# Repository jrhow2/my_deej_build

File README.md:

# jrhow2's Deej Build
## Description

This is a repository to document and share my work on my first Deej build, which includes 1 rotary potentiometer for master volume, 5 slide potentiometers, 6 latching mute 
buttons with LED indicators (one for each slider), and a 12-key macropad. This is primarily based on [miodec's fork](https://github.com/Miodec/deej), which 
adds support for programmable buttons to the original deej project from [omiharel](https://github.com/omriharel/deej).

The main additions I have made to these projects are the use of the [keypad.h](https://github.com/Chris--A/Keypad) library to increase the number of
programmable buttons past what would be achievable using the arduino nano's pins for individual buttons, and the use of latching led as mute buttons/LED indicators. An autohotkey script was used to expand the functionality of the programmable buttons, and a custom PCB was created to more easily add the macropad keyswitches.

In this repository, I've included that CAD files for the enclosure produced in Fusion360, the PCB schematics and gerber files, the customized arduino sketch, and the autohotkey script.

## Wokwi Cicuit design/code simulation
[Wokwi.com](https://wokwi.com) was used for circuit design and siumlation of the Arduino Nano and code. The Wokwi simulation can be found [here](https://wokwi.com/projects/416743878244643841), and the .zip files exported from Wokwi can be found at [deej_jrhow2_wokwi.zip](deej_jrhow2_wokwi.zip).

Note that since wokwi does not include latching buttons and because there was some difficulty with how I soldered my sliders in the final configuration, the code in wokwi does not exactly match the final code in the [provided .ino file](jrhow2s_deej.ino).

## [Mechancal Design](mechanical_design)
### Fusion 360 design files
The enclosure was designed in Fusion 360, and I've provided the [.f3d file](mechanical_design/f360_jrhow2's_deej.f3d).
### 3D printing
Slicing was performed in [Orca Slicer](https://github.com/SoftFever/OrcaSlicer) and the models were printed on a BambuLab P1S with an AMS unit for multi-color printing. I have provided the [Orca Slicer project file](mechanical_design/orca-slicer_jrhow2's_deej.3mf) as well as the [.stls](mechanical_design/STLs) of all of the parts.

To get the faux carbon fiber look on the top surface, I used [this textured plate](https://www.amazon.com/gp/product/B0CP5X3H2Z/ref=ppx_yo_dt_b_search_asin_title?ie=UTF8&psc=1) purchased from Amazon. These kinds of plates work best with slightly increased bed temperature and decreased speed for the first layer or two.

### Part's list
- [5x 60 mm Slide Potentiometers](https://www.amazon.com/dp/B07PNDLKQQ?ref_=ppx_hzsearch_conn_dt_b_fed_asin_title_1)
- [1x Rotary Potentiometer](https://www.amazon.com/dp/B07B64MWRF?ref_=ppx_hzsearch_conn_dt_b_fed_asin_title_2)
- [12x Cherry MX brown keyswitches](https://www.amazon.com/Cherry-MX-RGB-Mechanical-Keyboard/dp/B0CBS5M29R/ref=sr_1_2_sspa?crid=1GYDEP9RCY5T0&dib=eyJ2IjoiMSJ9.CN8d0MrS5DmQJVn-3xpAB0mhQuQKi8KCveO0JcbJzXpjdPU5HlAwrbz5tbdCWk3kthYGaP7PowyWtKo4o5DwA8xeNte1qEcJPl-tHwgDbC15iH93cMmkFZe0xWSh1AFUqjXYJmBKIA4P6uL1rWdwi3rx7YHnh_XPOvBDt01OFRK_tM1kTGipKEFM-LWU1gadXluddE0z2FO6sqxmrbP47VR9et4cIyCPHad9PMV20qwvgUSGjHwJ7VQUZ6RM5yiMxK3H-e-PVNU_TkNI8w8Ro4aga5POcPGEx3rvmk47ERo.JgLyCq7_-X_gLAnXje8SgQaPr5BdVQ0jFXflrShL0JE&dib_tag=se&keywords=cherry%2Bmx%2Bbrown%2Bkeyswitch&qid=1738734329&s=industrial&sprefix=cherry%2Bmx%2Bbrown%2Bkeyswitc%2Cindustrial%2C157&sr=1-2-spons&sp_csd=d2lkZ2V0TmFtZT1zcF9hdGY&smid=AK7PAPV76H5NA&th=1) (or similar)
- [6x Latching 12mm latching button with LED](https://www.amazon.com/dp/B09YLXBHF6?ref_=ppx_hzsearch_conn_dt_b_fed_asin_title_3&th=1) (2 per order)
- [Assort M2 screws](https://www.amazon.com/dp/B0BXS4SXYC?ref_=ppx_hzsearch_conn_dt_b_fed_asin_title_2) (a few of the holes are a bit shallower than others)
- [Elegoo Arduino Nano](https://www.amazon.com/ELEGOO-Arduino-ATmega328P-Without-Compatible/dp/B0713XK923/ref=sr_1_1_sspa?crid=2MQMFAE0FY1Z8&dib=eyJ2IjoiMSJ9.2thvq2A9ZsB75nwbFEpKLNare4EarLgE4_F7j-Bub2L3Dptzgt_789kuIaDLa3JEZPx4hOx-0XsgtrCr5ODgtectiKpfiS-EwMLYMbTm3-1Y0Ps6ziLABlBeyZnuvERKeSZlDR1-K9arOfYLnbvjHKibeIq8u-NfcilkmMGuvIkGhDF-UnZcuOMcGDx1Z1ZpTYCzasz53JTGUo3VJkckAOlmqv41opV5_m7QzFCSfjfq8PhjfRpXVy0oFbJLJ7DgswiqRYJJaj3ZVvBrdKsxvUVHj_74kFZ13D37oFWgwb4.3IOTlCk3ZtmxhoVleWZvcktHRexhEUHSoUZvN_WBMHw&dib_tag=se&keywords=elegoo+nano&qid=1738734462&s=industrial&sprefix=elegoo+nano%2Cindustrial%2C186&sr=1-1-spons&sp_csd=d2lkZ2V0TmFtZT1zcF9hdGY&psc=1)
- Wires, Solder, soldering iron, etc.

### 3D-printed Keycaps
I used [this parametric keycap generator](https://github.com/rsheldiii/KeyV2) with OpenSCAD to make flat keycaps for AMS printing with logos.

## PCB Design
I designed a keypad in KiCad. The PCB is very simple, just connecting the keyswitches together and including some contacts to solder on wires. The pcb files can be found [here](PCB/).

## Arduino Sketch
As mentioned above, my sketch is modified from [miodec's fork](https://github.com/Miodec/deej) by adding support for mute buttons and a keypad. The sketch can be found [here](arduino/jrhow2_deej/).

## Autohotkey script
I used Autohotkey to take the simple keyboard events sent by the arduino sketch and use them to support slightly more complex actions, such as launching apps and a "rage quit" button (just presses alt+f4). In [my config file](config.yaml), I tell Deej to send values for keys that are not commonly used by windows (e.g. "browser home"). Autohotkey then reads these and performs the desired actions. The autohotkey script can be found [here](autohotkey/deej_keys.ahk).

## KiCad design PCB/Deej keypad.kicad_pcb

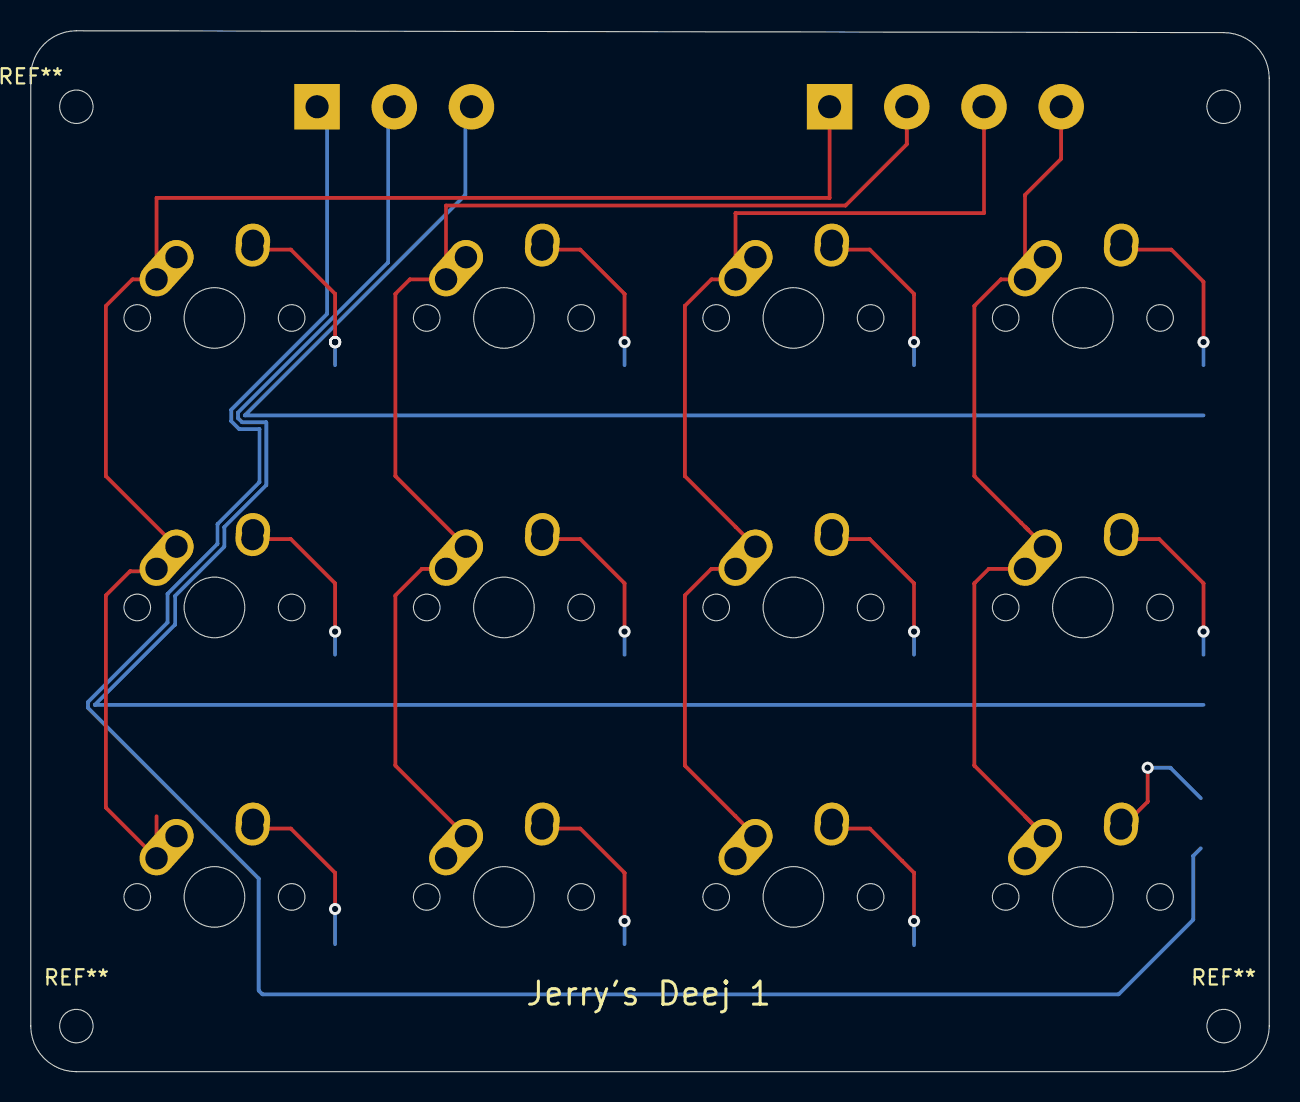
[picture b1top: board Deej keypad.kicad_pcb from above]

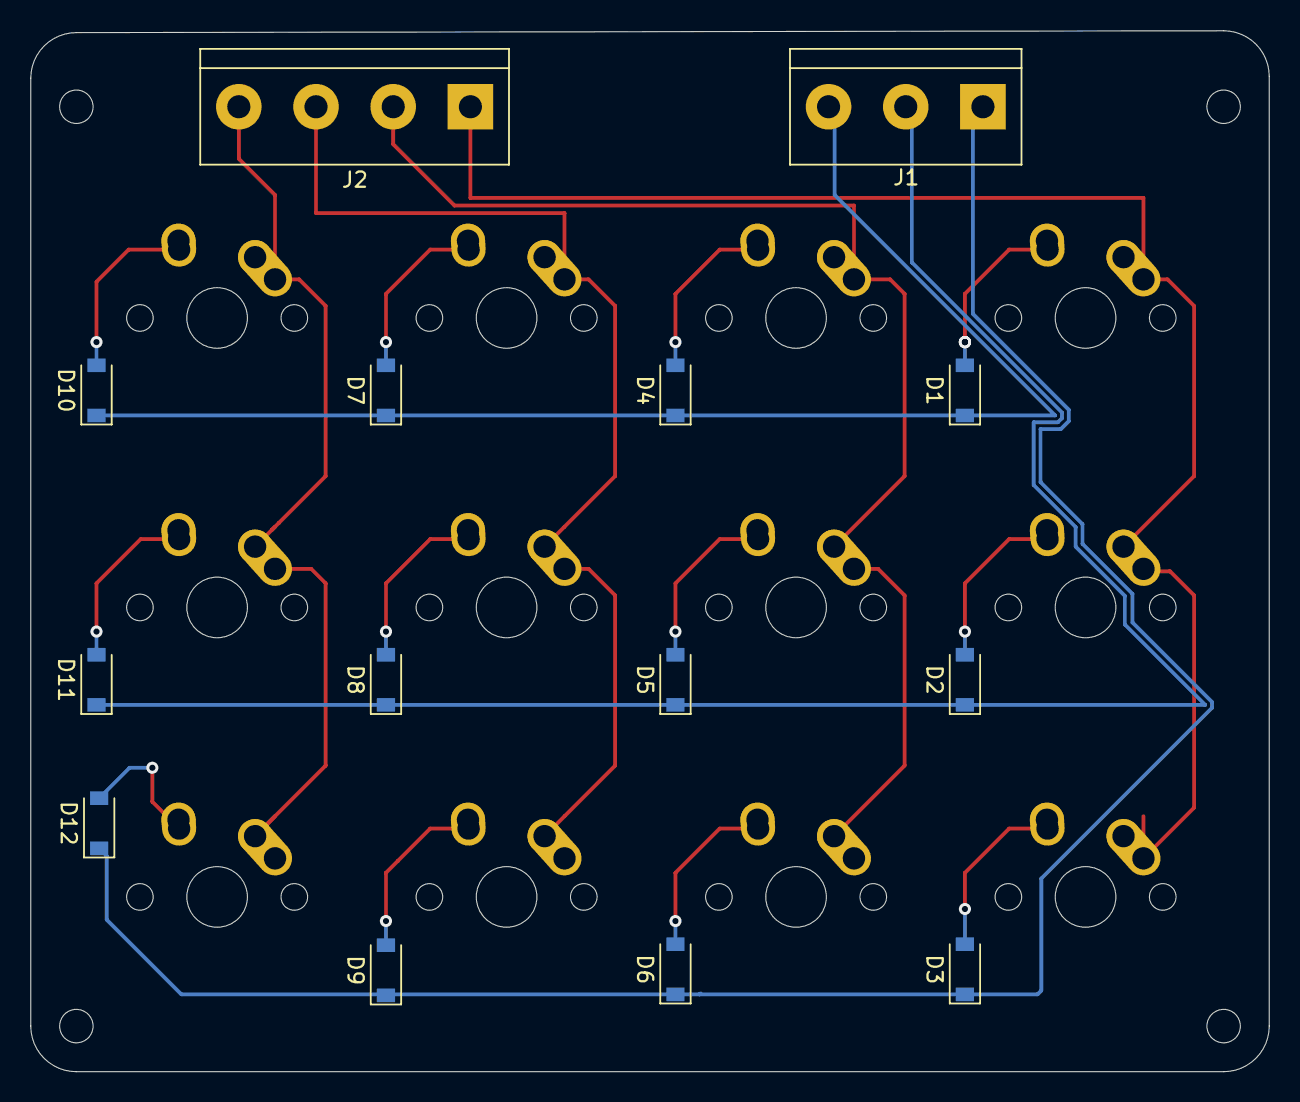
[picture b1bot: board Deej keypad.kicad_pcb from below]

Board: 2 copper layers, 81.5 x 68.5 mm, 26 parts (14 on the bottom side), 19 nets.

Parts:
D1, D2, D3, D4, D5, D6, D7, D8, D9, D10, D11, D12: D_Small; D_SOD-123
J1: Screw_Terminal_01x03; TerminalBlock_bornier-3_P5.08mm
J2: Screw_Terminal_01x04; TerminalBlock_bornier-4_P5.08mm
MX1, MX2, MX3, MX4, MX5, MX6, MX7, MX8, MX9, MX10, MX11, MX12: MX-NoLED; MX-1U-NoLED

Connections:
COL0: J2.1, MX1.1, MX2.1, MX3.1
COL1: J2.2, MX4.1, MX5.1, MX6.1
COL2: J2.3, MX7.1, MX8.1, MX9.1
COL3: J2.4, MX10.1, MX11.1, MX12.1
unnamed: D1.2, MX1.2
unnamed: D2.2, MX2.2
unnamed: D3.2, MX3.2
unnamed: D4.2, MX4.2
unnamed: D5.2, MX5.2
unnamed: D6.2, MX6.2
unnamed: D7.2, MX7.2
unnamed: D8.2, MX8.2
unnamed: D9.2, MX9.2
unnamed: D10.2, MX10.2
unnamed: D11.2, MX11.2
unnamed: D12.2, MX12.2
ROW0: D3.1, D6.1, D9.1, D12.1, J1.1
ROW1: D2.1, D5.1, D8.1, D11.1, J1.2
ROW2: D1.1, D4.1, D7.1, D10.1, J1.3

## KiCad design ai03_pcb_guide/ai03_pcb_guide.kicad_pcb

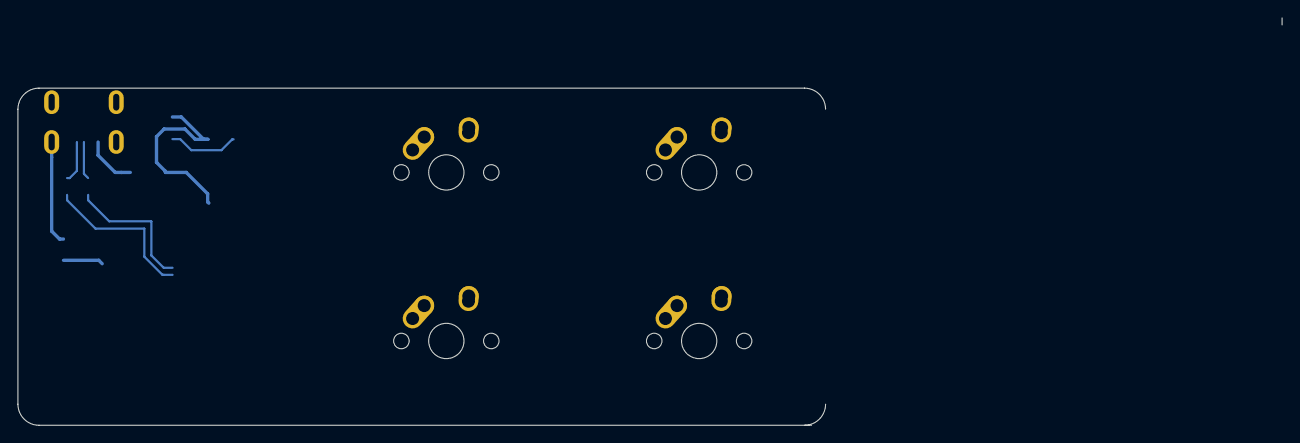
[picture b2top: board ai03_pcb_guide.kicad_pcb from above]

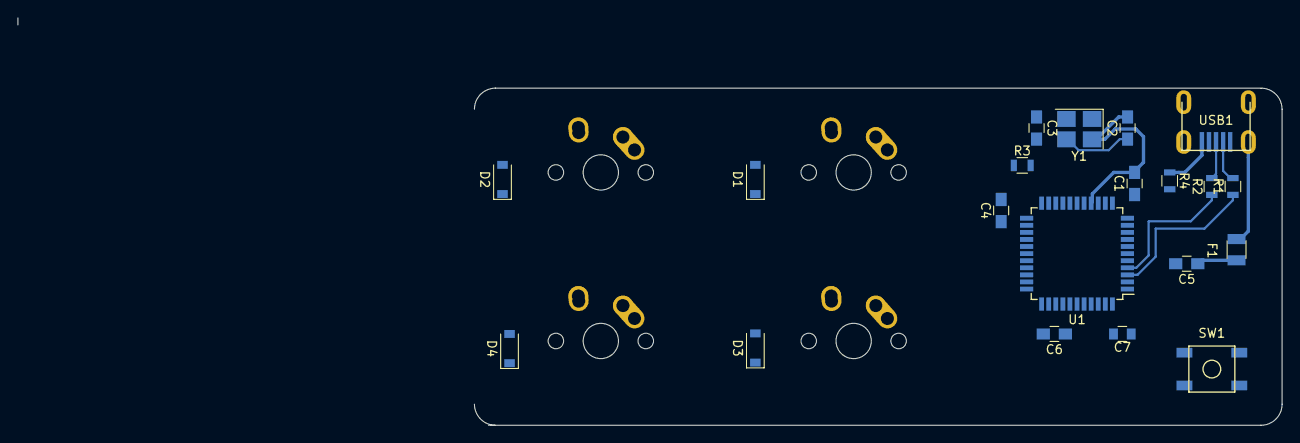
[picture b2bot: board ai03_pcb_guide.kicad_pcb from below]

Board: 2 copper layers, 142.9 x 46.0 mm, 24 parts (20 on the bottom side), 20 nets.

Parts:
C1, C4, C5: 0.1 uF; C_0805_HandSoldering
C2, C3: 22pF; C_0805_HandSoldering
C6: 1 uF; C_0805_HandSoldering
C7: 10 uF; C_0805
D1, D2, D3, D4: D_Small; D_SOD-123
F1: 500 mA; Fuse_SMD1206_Reflow
MX1, MX2, MX3, MX4: MX-NoLED; MX-1.5U-NoLED
R1, R2: 22; R_0805
R3, R4: 10k; R_0805
SW1: SW_Push; SKQG-1155865
U1: ATmega32U4-AU; TQFP-44_10x10mm_Pitch0.8mm
USB1: Molex-0548190589
Y1: 16 MHz; Crystal_SMD_3225-4pin_3.2x2.5mm_HandSoldering

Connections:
+5V: C1.1, C4.1, C5.1, C7.1, F1.1, R3.1, U1.2, U1.7, U1.14, U1.24, U1.34, U1.44
COL0: MX1.1, MX2.1
COL1: MX3.1, MX4.1
D+: R2.2, USB1.3
D-: R1.2, USB1.4
GND: C1.2, C2.2, C3.2, C4.2, C5.2, C6.2, C7.2, R4.1, SW1.1, U1.5, U1.15, U1.23, U1.35, U1.43, USB1.1, Y1.2, Y1.4
unnamed: C2.1, U1.16, Y1.3
unnamed: C3.1, U1.17, Y1.1
unnamed: C6.1, U1.6
unnamed: D1.2, MX1.2
unnamed: D2.2, MX2.2
unnamed: D3.2, MX3.2
unnamed: D4.2, MX4.2
unnamed: R1.1, U1.3
unnamed: R2.1, U1.4
unnamed: R3.2, SW1.2, U1.13
unnamed: R4.2, U1.33
ROW0: D1.1, D3.1
ROW1: D2.1, D4.1
VCC: F1.2, USB1.6

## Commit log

2024-12-09 Initializing with KiCad files
2024-12-09 Add submodules
2024-12-09 Switched to older version for compatibility with guide
2024-12-09 Added libraries to pcb editor
2024-12-09 Started designing PCB for deej keypad
2024-12-09 saving changes
2025-01-01 Uploaded main files for running deej
    Uploaded config.yaml, autohotkey script, and arduino sketch.
2025-01-02 Added wokwi zip archive
2025-01-02 Rename Deej_Soldered.ino to jrhow2s_deej.ino
2025-01-02 Rename Jrhow2's Deej.f3d to Mechanical Design/Jrhow2's Deej.f3d
2025-01-02 Rename Deej top face 20241220.3mf to jrhow2's deej.3mf
2025-01-02 Rename mechanical_design/Badge_support.stl to mechanical_design/STLs/badge_support.stl
2025-01-02 Rename mechanical_design/Key Frame.step.stl to mechanical_design/STLs/key_frame.stl
2025-01-02 Rename mechanical_design/PCB_support.stl to mechanical_design/STLs/PCB_support.stl
2025-01-02 Rename mechanical_design/bottom_casing.stl to mechanical_design/STLs/bottom_casing.stl
2025-01-02 Rename mechanical_design/face_plate.stl to mechanical_design/STLs/face_plate.stl
2025-01-02 Rename mechanical_design/flat_keycap.stl to mechanical_design/STLs/flat_keycap.stl
2025-01-02 Rename mechanical_design/logo_badge.stl to mechanical_design/STLs/logo_badge.stl
2025-01-02 Rename mechanical_design/slider_support.stl to mechanical_design/STLs/slider_support.stl
2025-01-02 Rename mechanical_design/slider.stl to mechanical_design/STLs/slider.stl
2025-02-05 replace the broken f3d file
2025-02-05 fixed the broke orca slicer .3mf
2025-02-05 deleted old .3mf file
2025-02-05 Update README.md
    Updated parts list
2025-02-05 Update README.md
    Added link for screws I used
2025-02-05 Update README.md
    Added link to openscad keycaps.
2025-02-05 Added PCB files for KiCad
2025-02-05 Update README.md
    Added PCB details to README
2025-02-05 added arduino sketch and autohotkey file
2025-02-05 modified autohotkey script
2025-02-05 Update README.md
    Added arduino and autohotkey details to README.
2025-02-05 Update README.md
    fixed link to arduino sketch.
2025-02-05 updated config.yaml
